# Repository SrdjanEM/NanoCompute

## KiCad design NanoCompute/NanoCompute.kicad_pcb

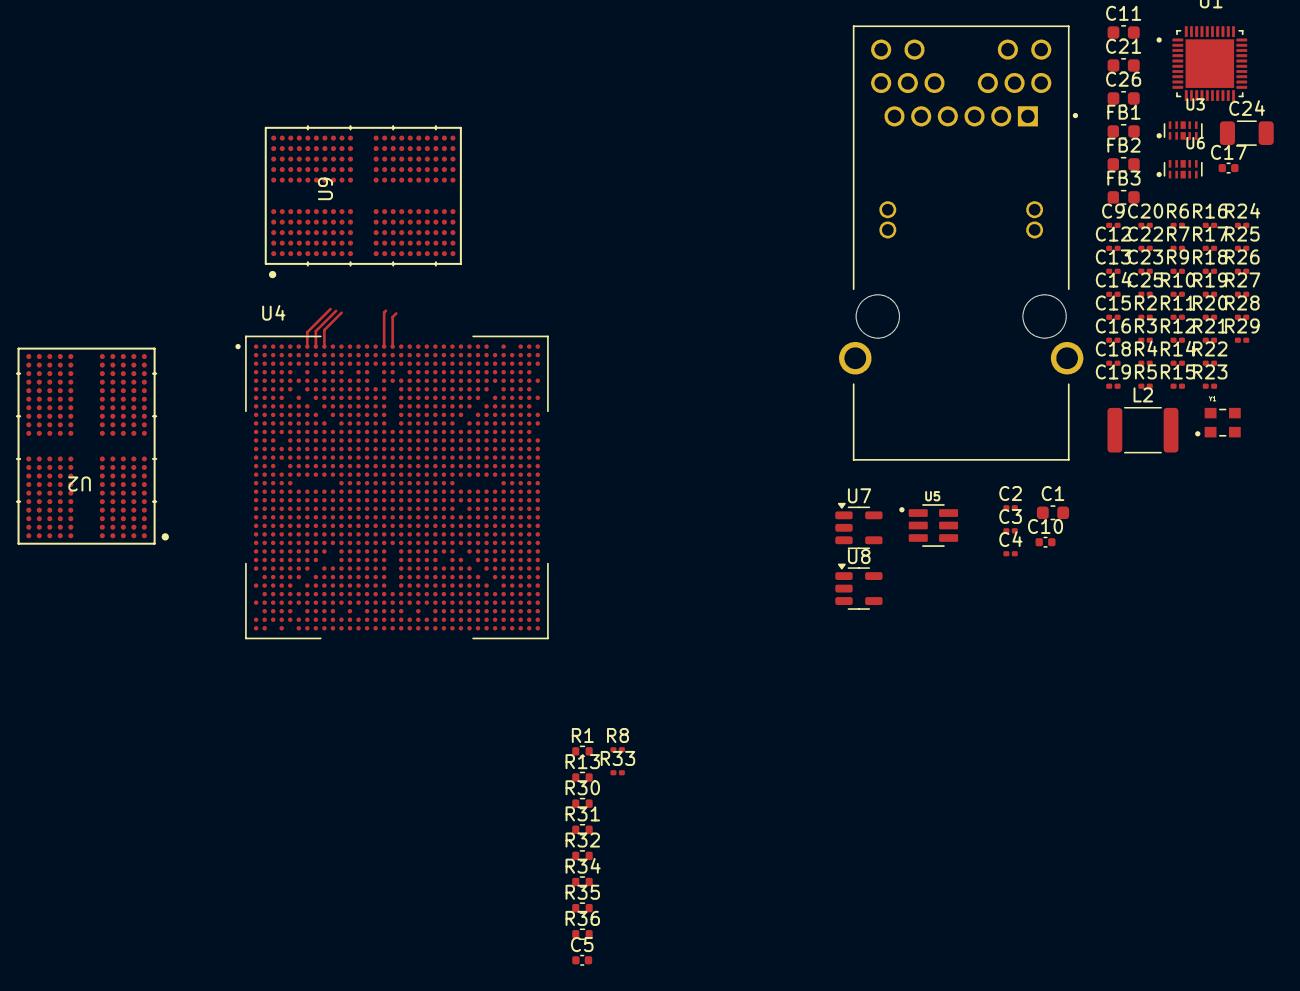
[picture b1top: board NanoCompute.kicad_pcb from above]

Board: 2 copper layers, 74 parts (0 on the bottom side), 184 nets.

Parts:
C1, C11, C21, C26: 10u; C_0603_1608Metric
C2: 1u; C_0201_0603Metric
C3, C9, C12, C13, C14, C15, C16, C18, C19, C20, C22, C23, C25: 100n; C_0201_0603Metric
C4: 10n; C_0201_0603Metric
C5: 100n; C_0402_1005Metric
C10, C17: 4u7; C_0402_1005Metric
C24: 1n / 2kV; C_1206_3216Metric
FB1, FB2, FB3: 120R @ 100MHz; L_0603_1608Metric
J1: 2250506; BEL_2250506-1
L2: 2u2; L_1812_4532Metric
R1, R13, R30, R31, R32, R34, R35, R36: 240R; R_0402_1005Metric
R2, R3, R4, R5, R6, R7: 33R; R_0201_0603Metric
R8, R33: 10K; R_0201_0603Metric
R9, R10, R11, R14, R15, R16, R17, R18, R19, R20, R21, R22, R23, R24, R25, R26, R27: 4K7; R_0201_0603Metric
R12: 1K5; R_0201_0603Metric
R28, R29: 510R; R_0201_0603Metric
U1: RTL8211F; RTL8211F-CG
U2, U9: MT53E1G32D2FW; VFBGA200_10X14.5X1.1FW_MRN
U3, U6: HSP051; IC_HSP051-4M10
U4: RK3588; BGA1088C65P34X34_2300X2300X204N
U5: TPS54308; TPS54308DDCR
U7: TLV74311; SOT-23-5
U8: TLV74325; SOT-23-5
Y1: 25 MHz; OSC_ECS-2520S25-250-FN-TR

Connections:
+1V8: C16.1, FB3.1
+1VA8: C21.1, C22.1, FB3.2, R9.1, U1.28 (DVDD_RG)
+3V3: C9.1, C11.1, FB2.1, R11.1, R12.1, R15.1, R17.1, R25.1, U1.13 (MDC), U1.29 (DVDD33), Y1.4 (VDD)
+3VA3: C12.1, C13.1, FB2.2, R19.1, R20.1, R24.1, U1.11 (AVDD33), U1.40 (AVDD33)
/Ethernet PHY/ETH_HWRESET: C23.1, R9.2, U1.12 (PHYRSTB)
/Ethernet PHY/ETH_MDUI: R12.2, U1.14 (MDIO)
/Ethernet PHY/ETH_RESET: R10.1, U1.39 (RSET)
/Ethernet PHY/LED0/CFG_EXT: J1.20, R25.2, U1.32 (LED0/CFG_EXT)
/Ethernet PHY/LED1/CFG_LDO0: J1.18, R27.1, U1.33 (LED1/CFG_LDO0)
/Ethernet PHY/LED2/CFG_LDO1: R26.1, U1.34 (LED2/CFG_LDO1)
/Ethernet PHY/PHYAD0: R5.2, R11.2, R14.1
/Ethernet PHY/PHYAD1: R6.2, R15.2, R16.1
/Ethernet PHY/PHYAD2: R7.2, R17.2, R18.1
/Ethernet PHY/PHY_ADVDDL: C15.1, C19.1, C20.1, FB1.2, U1.3 (AVDD10), U1.8 (AVDD10), U1.38 (AVDD10)
/Ethernet PHY/PHY_DVDDL: C14.1, C17.1, C18.1, FB1.1, L2.2, U1.21 (DVDD10)
/Ethernet PHY/PLLOFF: R4.2, R23.1, R24.2
/Ethernet PHY/RXDLY: R2.2, R19.2, R21.1
/Ethernet PHY/TP_1_N: J1.10 (TRD1-), U1.2 (MDIN0), U3.2 (I/O_2)
/Ethernet PHY/TP_1_P: J1.11 (TRD1+), U1.1 (MDIP0), U3.1 (I/O_1)
/Ethernet PHY/TP_2_N: J1.5 (TRD2-), U1.5 (MDIN1), U3.5 (I/O_4)
/Ethernet PHY/TP_2_P: J1.4 (TRD2+), U1.4 (MDIP1), U3.4 (I/O_3)
/Ethernet PHY/TP_3_N: J1.2 (TRD3-), U1.7 (MDIN2), U6.2 (I/O_2)
/Ethernet PHY/TP_3_P: J1.3 (TRD3+), U1.6 (MDIP2), U6.1 (I/O_1)
/Ethernet PHY/TP_4_N: J1.9 (TRD4-), U1.10 (MDIN3), U6.5 (I/O_4)
/Ethernet PHY/TP_4_P: J1.8 (TRD4+), U1.9 (MDIP3), U6.4 (I/O_3)
/Ethernet PHY/TRCTx: C25.1, C26.1, J1.1 (TRCT3), J1.6 (TRCT2), J1.7 (TRCT4), J1.12 (TRCT1)
/Ethernet PHY/TXDLY: R3.2, R20.2, R22.1
/LPDDR4/CA0_A: U2.H2 (CA0_A), U4.T7 (DDR_CH0_A0_A)
/LPDDR4/CA0_B: U2.R2 (CA0_B), U4.M8 (DDR_CH0_A0_B)
/LPDDR4/CA0_C: U4.G12 (DDR_CH1_A0_C), U9.H2 (CA0_A)
/LPDDR4/CA0_D: U4.H15 (DDR_CH1_A0_D), U9.R2 (CA0_B)
/LPDDR4/CA1_A: U2.J2 (CA1_A), U4.T8 (DDR_CH0_A1_A)
/LPDDR4/CA1_B: U2.P2 (CA1_B), U4.M5 (DDR_CH0_A1_B)
/LPDDR4/CA1_C: U4.F12 (DDR_CH1_A1_C), U9.J2 (CA1_A)
/LPDDR4/CA1_D: U4.G14 (DDR_CH1_A1_D), U9.P2 (CA1_B)
/LPDDR4/CA2_A: U2.H9 (CA2_A), U4.P4 (DDR_CH0_A2_A)
/LPDDR4/CA2_B: U2.R9 (CA2_B), U4.N5 (DDR_CH0_A2_B)
/LPDDR4/CA2_C: U4.E13 (DDR_CH1_A2_C), U9.H9 (CA2_A)
/LPDDR4/CA2_D: U4.G13 (DDR_CH1_A2_D), U9.R9 (CA2_B)
/LPDDR4/CA3_A: U2.H10 (CA3_A), U4.P5 (DDR_CH0_A3_A)
/LPDDR4/CA3_B: U2.R10 (CA3_B), U4.N4 (DDR_CH0_A3_B)
/LPDDR4/CA3_C: U4.D13 (DDR_CH1_A3_C), U9.H10 (CA3_A)
/LPDDR4/CA3_D: U4.E14 (DDR_CH1_A3_D), U9.R10 (CA3_B)
/LPDDR4/CA4_A: U2.H11 (CA4_A), U4.R1 (DDR_CH0_A4_A)
/LPDDR4/CA4_B: U2.R11 (CA4_B), U4.K1 (DDR_CH0_A4_B)
/LPDDR4/CA4_C: U4.A10 (DDR_CH1_A4_C), U9.H11 (CA4_A)
/LPDDR4/CA4_D: U4.A15 (DDR_CH1_A4_D), U9.R11 (CA4_B)
/LPDDR4/CA5_A: U2.J11 (CA5_A), U4.P2 (DDR_CH0_A5_A)
/LPDDR4/CA5_B: U2.P11 (CA5_B), U4.L2 (DDR_CH0_A5_B)
/LPDDR4/CA5_C: U4.B11 (DDR_CH1_A5_C), U9.J11 (CA5_A)
/LPDDR4/CA5_D: U4.B14 (DDR_CH1_A5_D), U9.P11 (CA5_B)
/LPDDR4/CKE0_A: U2.J4 (CKE0_A), U4.P7 (DDR_CH0_LP4/4X_CKE0/LP5_CS0_A)
/LPDDR4/CKE0_B: U2.P4 (CKE0_B), U4.L5 (DDR_CH0_LP4/4X_CKE0/LP5_CS0_B)
/LPDDR4/CKE0_C: U4.D11 (DDR_CH1_LP4/4X_CKE0/LP5_CS0_C), U9.J4 (CKE0_A)
/LPDDR4/CKE0_D: U4.D16 (DDR_CH1_LP4/4X_CKE0/LP5_CS0_D), U9.P4 (CKE0_B)
/LPDDR4/CKE1_A: U2.J5 (CKE1_A), U4.N7 (DDR_CH0_LP4/4X_CKE1/LP5_CS1_A)
/LPDDR4/CKE1_B: U2.P5 (CKE1_B), U4.L4 (DDR_CH0_LP4/4X_CKE1/LP5_CS1_B)
/LPDDR4/CKE1_C: U4.E11 (DDR_CH1_LP4/4X_CKE1/LP5_CS1_C), U9.J5 (CKE1_A)
/LPDDR4/CKE1_D: U4.E16 (DDR_CH1_LP4/4X_CKE1/LP5_CS1_D), U9.P5 (CKE1_B)
/LPDDR4/CK_A_N: U2.J9 (CK_c_A), U2.P9 (CK_c_B), U4.M1 (DDR_CH0_CKB_B), U4.N1 (DDR_CH0_CKB_A)
/LPDDR4/CK_A_P: U2.J8 (CK_t_A), U2.P8 (CK_t_B), U4.M2 (DDR_CH0_CK_B), U4.N2 (DDR_CH0_CK_A)
/LPDDR4/CK_C_N: U4.A12 (DDR_CH1_CKB_C), U9.J9 (CK_c_A)
/LPDDR4/CK_C_P: U4.B12 (DDR_CH1_CK_C), U9.J8 (CK_t_A)
/LPDDR4/CK_D_N: U4.A13 (DDR_CH1_CKB_D), U9.P9 (CK_c_B)
/LPDDR4/CK_D_P: U4.B13 (DDR_CH1_CK_D), U9.P8 (CK_t_B)
/LPDDR4/CS0_A: U2.H4 (CS0_A), U4.R6 (DDR_CH0_LP4/4X_CS0_A)
/LPDDR4/CS0_B: U2.R4 (CS0_B), U4.L7 (DDR_CH0_LP4/4X_CS0_B)
/LPDDR4/CS0_C: U4.G11 (DDR_CH1_LP4/4X_CS0_C), U9.H4 (CS0_A)
/LPDDR4/CS0_D: U4.E19 (DDR_CH1_LP4/4X_CS0_D), U9.R4 (CS0_B)
/LPDDR4/CS1_A: U2.H3 (CS1_A), U4.R7 (DDR_CH0_LP4/4X_CS1_A)
/LPDDR4/CS1_B: U2.R3 (CS1_B), U4.L8 (DDR_CH0_LP4/4X_CS1_B)
/LPDDR4/CS1_C: U4.H11 (DDR_CH1_LP4/4X_CS1_C), U9.H3 (CS1_A)
/LPDDR4/CS1_D: U4.D19 (DDR_CH1_LP4/4X_CS1_D), U9.R3 (CS1_B)
/LPDDR4/DMI1_A: U2.C10 (DMI1_A), U4.AB4 (DDR_CH0_DM1_A)
/LPDDR4/DMI1_B: U2.Y10 (DMI1_B), U4.E4 (DDR_CH0_DM1_B)
/LPDDR4/DMI1_C: U4.D4 (DDR_CH1_DM1_C), U9.C10 (DMI1_A)
/LPDDR4/DMI1_D: U4.D22 (DDR_CH1_DM1_D), U9.Y10 (DMI1_B)
/LPDDR4/DMIO_A: U2.C3 (DMI0_A), U4.Y4 (DDR_CH0_DM0_A)
/LPDDR4/DMIO_B: U2.Y3 (DMI0_B), U4.G4 (DDR_CH0_DM0_B)
/LPDDR4/DMIO_C: U4.F8 (DDR_CH1_DM0_C), U9.C3 (DMI0_A)
/LPDDR4/DMIO_D: U4.D20 (DDR_CH1_DM0_D), U9.Y3 (DMI0_B)
/LPDDR4/DQ0_A: U2.B2 (DQ0_A), U4.U1 (DDR_CH0_DQ0_A)
/LPDDR4/DQ0_B: U2.AA2 (DQ0_B), U4.H1 (DDR_CH0_DQ0_B)
/LPDDR4/DQ0_C: U4.A8 (DDR_CH1_DQ0_C), U9.B2 (DQ0_A)
/LPDDR4/DQ0_D: U4.A17 (DDR_CH1_DQ0_D), U9.AA2 (DQ0_B)
/LPDDR4/DQ1_A: U2.C2 (DQ1_A), U4.T2 (DDR_CH0_DQ1_A)
/LPDDR4/DQ1_B: U2.Y2 (DQ1_B), U4.J2 (DDR_CH0_DQ1_B)
/LPDDR4/DQ1_C: U4.B9 (DDR_CH1_DQ1_C), U9.C2 (DQ1_A)
/LPDDR4/DQ1_D: U4.B16 (DDR_CH1_DQ1_D), U9.Y2 (DQ1_B)
/LPDDR4/DQ2_A: U2.E2 (DQ2_A), U4.T1 (DDR_CH0_DQ2_A)
/LPDDR4/DQ2_B: U2.V2 (DQ2_B), U4.J1 (DDR_CH0_DQ2_B)
/LPDDR4/DQ2_C: U4.A9 (DDR_CH1_DQ2_C), U9.E2 (DQ2_A)
/LPDDR4/DQ2_D: U4.A16 (DDR_CH1_DQ2_D), U9.V2 (DQ2_B)
/LPDDR4/DQ3_A: U2.F2 (DQ3_A), U4.R2 (DDR_CH0_DQ3_A)
/LPDDR4/DQ3_B: U2.U2 (DQ3_B), U4.K2 (DDR_CH0_DQ3_B)
/LPDDR4/DQ3_C: U4.B10 (DDR_CH1_DQ3_C), U9.F2 (DQ3_A)
/LPDDR4/DQ3_D: U4.B15 (DDR_CH1_DQ3_D), U9.U2 (DQ3_B)
/LPDDR4/DQ4_A: U2.F4 (DQ4_A), U4.W1 (DDR_CH0_DQ4_A)
/LPDDR4/DQ4_B: U2.U4 (DQ4_B), U4.F1 (DDR_CH0_DQ4_B)
/LPDDR4/DQ4_C: U4.A6 (DDR_CH1_DQ4_C), U9.F4 (DQ4_A)
/LPDDR4/DQ4_D: U4.A19 (DDR_CH1_DQ4_D), U9.U4 (DQ4_B)
/LPDDR4/DQ5_A: U2.E4 (DQ5_A), U4.V2 (DDR_CH0_DQ5_A)
/LPDDR4/DQ5_B: U2.V4 (DQ5_B), U4.G2 (DDR_CH0_DQ5_B)
/LPDDR4/DQ5_C: U4.B7 (DDR_CH1_DQ5_C), U9.E4 (DQ5_A)
/LPDDR4/DQ5_D: U4.B18 (DDR_CH1_DQ5_D), U9.V4 (DQ5_B)
/LPDDR4/DQ6_A: U2.C4 (DQ6_A), U4.V1 (DDR_CH0_DQ6_A)
/LPDDR4/DQ6_B: U2.Y4 (DQ6_B), U4.G1 (DDR_CH0_DQ6_B)
/LPDDR4/DQ6_C: U4.A7 (DDR_CH1_DQ6_C), U9.C4 (DQ6_A)
/LPDDR4/DQ6_D: U4.A18 (DDR_CH1_DQ6_D), U9.Y4 (DQ6_B)
/LPDDR4/DQ7_A: U2.B4 (DQ7_A), U4.U2 (DDR_CH0_DQ7_A)
/LPDDR4/DQ7_B: U2.AA4 (DQ7_B), U4.H2 (DDR_CH0_DQ7_B)
/LPDDR4/DQ7_C: U4.B8 (DDR_CH1_DQ7_C), U9.B4 (DQ7_A)
/LPDDR4/DQ7_D: U4.B17 (DDR_CH1_DQ7_D), U9.AA4 (DQ7_B)
/LPDDR4/DQ8_A: U2.B11 (DQ8_A), U4.AB2 (DDR_CH0_DQ8_A)
/LPDDR4/DQ8_B: U2.AA11 (DQ8_B), U4.D2 (DDR_CH0_DQ8_B)
/LPDDR4/DQ8_C: U4.A3 (DDR_CH1_DQ8_C), U9.B11 (DQ8_A)
/LPDDR4/DQ8_D: U4.A22 (DDR_CH1_DQ8_D), U9.AA11 (DQ8_B)
/LPDDR4/DQ9_A: U2.C11 (DQ9_A), U4.AB1 (DDR_CH0_DQ9_A)
/LPDDR4/DQ9_B: U2.Y11 (DQ9_B), U4.C1 (DDR_CH0_DQ9_B)
/LPDDR4/DQ9_C: U4.B3 (DDR_CH1_DQ9_C), U9.C11 (DQ9_A)
/LPDDR4/DQ9_D: U4.B22 (DDR_CH1_DQ9_D), U9.Y11 (DQ9_B)
/LPDDR4/DQ10_A: U2.E11 (DQ10_A), U4.AC1 (DDR_CH0_DQ10_A)
/LPDDR4/DQ10_B: U2.V11 (DQ10_B), U4.C2 (DDR_CH0_DQ10_B)
/LPDDR4/DQ10_C: U4.A2 (DDR_CH1_DQ10_C), U9.E11 (DQ10_A)
/LPDDR4/DQ10_D: U4.A23 (DDR_CH1_DQ10_D), U9.V11 (DQ10_B)
/LPDDR4/DQ11_A: U2.F11 (DQ11_A), U4.AC2 (DDR_CH0_DQ11_A)
/LPDDR4/DQ11_B: U2.U11 (DQ11_B), U4.B1 (DDR_CH0_DQ11_B)
/LPDDR4/DQ11_C: U4.B2 (DDR_CH1_DQ11_C), U9.F11 (DQ11_A)
/LPDDR4/DQ11_D: U4.B23 (DDR_CH1_DQ11_D), U9.U11 (DQ11_B)
/LPDDR4/DQ12_A: U2.F9 (DQ12_A), U4.Y1 (DDR_CH0_DQ12_A)
/LPDDR4/DQ12_B: U2.U9 (DQ12_B), U4.F2 (DDR_CH0_DQ12_B)
/LPDDR4/DQ12_C: U4.A5 (DDR_CH1_DQ12_C), U9.F9 (DQ12_A)
/LPDDR4/DQ12_D: U4.A20 (DDR_CH1_DQ12_D), U9.U9 (DQ12_B)
/LPDDR4/DQ13_A: U2.E9 (DQ13_A), U4.Y2 (DDR_CH0_DQ13_A)
/LPDDR4/DQ13_B: U2.V9 (DQ13_B), U4.E1 (DDR_CH0_DQ13_B)
/LPDDR4/DQ13_C: U4.B5 (DDR_CH1_DQ13_C), U9.E9 (DQ13_A)
/LPDDR4/DQ13_D: U4.B20 (DDR_CH1_DQ13_D), U9.V9 (DQ13_B)
/LPDDR4/DQ14_A: U2.C9 (DQ14_A), U4.AA1 (DDR_CH0_DQ14_A)
/LPDDR4/DQ14_B: U2.Y9 (DQ14_B), U4.E2 (DDR_CH0_DQ14_B)
/LPDDR4/DQ14_C: U4.A4 (DDR_CH1_DQ14_C), U9.C9 (DQ14_A)
/LPDDR4/DQ14_D: U4.A21 (DDR_CH1_DQ14_D), U9.Y9 (DQ14_B)
/LPDDR4/DQ15_A: U2.B9 (DQ15_A), U4.AA2 (DDR_CH0_DQ15_A)
/LPDDR4/DQ15_B: U2.AA9 (DQ15_B), U4.D1 (DDR_CH0_DQ15_B)
/LPDDR4/DQ15_C: U4.B4 (DDR_CH1_DQ15_C), U9.B9 (DQ15_A)
/LPDDR4/DQ15_D: U4.B21 (DDR_CH1_DQ15_D), U9.AA9 (DQ15_B)
/LPDDR4/DQS0_A_N: U2.E3 (DQS0_c_A), U4.U4 (DDR_CH0_DQS0N_A)
/LPDDR4/DQS0_A_P: U2.D3 (DQS0_t_A), U4.U5 (DDR_CH0_DQS0P_A)
/LPDDR4/DQS0_B_N: U2.V3 (DQS0_c_B), U4.J7 (DDR_CH0_DQS0N_B)
/LPDDR4/DQS0_B_P: U2.W3 (DQS0_t_B), U4.J8 (DDR_CH0_DQS0P_B)
/LPDDR4/DQS0_C_N: U4.D9 (DDR_CH1_DQS0N_C), U9.E3 (DQS0_c_A)
/LPDDR4/DQS0_C_P: U4.E9 (DDR_CH1_DQS0P_C), U9.D3 (DQS0_t_A)
/LPDDR4/DQS0_D_N: U4.G16 (DDR_CH1_DQS0N_D), U9.V3 (DQS0_c_B)
/LPDDR4/DQS0_D_P: U4.H16 (DDR_CH1_DQS0P_D), U9.W3 (DQS0_t_B)
/LPDDR4/DQS1_A_N: U2.E10 (DQS1_c_A), U4.AA4 (DDR_CH0_DQS1N_A)
/LPDDR4/DQS1_A_P: U2.D10 (DQS1_t_A), U4.AA5 (DDR_CH0_DQS1P_A)
/LPDDR4/DQS1_B_N: U2.V10 (DQS1_c_B), U4.F4 (DDR_CH0_DQS1N_B)
/LPDDR4/DQS1_B_P: U2.W10 (DQS1_t_B), U4.F5 (DDR_CH0_DQS1P_B)
/LPDDR4/DQS1_C_N: U4.D5 (DDR_CH1_DQS1N_C), U9.E10 (DQS1_c_A)
/LPDDR4/DQS1_C_P: U4.E5 (DDR_CH1_DQS1P_C), U9.D10 (DQS1_t_A)
/LPDDR4/DQS1_D_N: U4.E21 (DDR_CH1_DQS1N_D), U9.V10 (DQS1_c_B)
/LPDDR4/DQS1_D_P: U4.D21 (DDR_CH1_DQS1P_D), U9.W10 (DQS1_t_B)
/LPDDR4/~RESET_AB: R8.1, U2.T11 (RESET_n), U4.T4 (DDR_CH0_RESET_A)
/LPDDR4/~RESET_CD: R33.1, U4.E10 (DDR_CH1_RESET_C), U9.T11 (RESET_n)
GND: C9.2, C11.2, C12.2, C13.2, C14.2, C15.2, C16.2, C17.2, C18.2, C19.2, C20.2, C21.2, C22.2, C23.2, C24.2, C25.2, C26.2, R8.2, R10.2, R14.2, R16.2, R18.2, R21.2, R22.2, R23.2, R26.2, R27.2, R28.2, R29.2, R30.2, R31.2, R33.2, R35.2, R36.2, U1.36 (XTAL_IN), U1.41 (GND), U2.A3 (VSS), U2.A10 (VSS), U2.AB3 (VSS), U2.AB5 (VSS), U2.AB8 (VSS), U2.AB10 (VSS), U2.C1 (VSS), U2.C5 (VSS), U2.C8 (VSS), U2.C12 (VSS), U2.D2 (VSS), U2.D4 (VSS), U2.D9 (VSS), U2.D11 (VSS), U2.E1 (VSS), U2.E5 (VSS), U2.E8 (VSS), U2.E12 (VSS), U2.G1 (VSS), U2.G3 (VSS), U2.G5 (VSS), U2.G8 (VSS), U2.G10 (VSS), U2.G12 (VSS), U2.J1 (VSS), U2.J3 (VSS), U2.J10 (VSS), U2.J12 (VSS), U2.K2 (VSS), U2.K4 (VSS), U2.K9 (VSS), U2.K11 (VSS), U2.N2 (VSS), U2.N4 (VSS), U2.N9 (VSS), U2.N11 (VSS), U2.P1 (VSS), U2.P3 (VSS), U2.P10 (VSS), U2.P12 (VSS), U2.T1 (VSS), U2.T3 (VSS), U2.T5 (VSS), U2.T8 (VSS), U2.T10 (VSS), U2.T12 (VSS), U2.V1 (VSS), U2.V5 (VSS), U2.V8 (VSS), U2.V12 (VSS), U2.W2 (VSS), U2.W4 (VSS), U2.W9 (VSS), U2.W11 (VSS), U2.Y1 (VSS), U2.Y5 (VSS), U2.Y8 (VSS), U2.Y12 (VSS), U3.3 (GND), U3.8 (GND__1), U4.L16 (DDR_CH1_PLL_AVSS), U4.M11 (DDR_CH0_PLL_AVSS), U6.3 (GND), U6.8 (GND__1), U9.A3 (VSS), U9.A10 (VSS), U9.AB3 (VSS), U9.AB5 (VSS), U9.AB8 (VSS), U9.AB10 (VSS), U9.C1 (VSS), U9.C5 (VSS), U9.C8 (VSS), U9.C12 (VSS), U9.D2 (VSS), U9.D4 (VSS), U9.D9 (VSS), U9.D11 (VSS), U9.E1 (VSS), U9.E5 (VSS), U9.E8 (VSS), U9.E12 (VSS), U9.G1 (VSS), U9.G3 (VSS), U9.G5 (VSS), U9.G8 (VSS), U9.G10 (VSS), U9.G12 (VSS), U9.J1 (VSS), U9.J3 (VSS), U9.J10 (VSS), U9.J12 (VSS), U9.K2 (VSS), U9.K4 (VSS), U9.K9 (VSS), U9.K11 (VSS), U9.N2 (VSS), U9.N4 (VSS), U9.N9 (VSS), U9.N11 (VSS), U9.P1 (VSS), U9.P3 (VSS), U9.P10 (VSS), U9.P12 (VSS), U9.T1 (VSS), U9.T3 (VSS), U9.T5 (VSS), U9.T8 (VSS), U9.T10 (VSS), U9.T12 (VSS), U9.V1 (VSS), U9.V5 (VSS), U9.V8 (VSS), U9.V12 (VSS), U9.W2 (VSS), U9.W4 (VSS), U9.W9 (VSS), U9.W11 (VSS), U9.Y1 (VSS), U9.Y5 (VSS), U9.Y8 (VSS), U9.Y12 (VSS), Y1.2 (GND)
unnamed: C24.1, J1.S1 (SHIELD), J1.S2 (SHIELD)
unnamed: J1.17, R29.1
unnamed: J1.19, R28.1
unnamed: L2.1, U1.30 (REG_OUT)
unnamed: R7.1, U1.26 (RXCTL/PHYAD2)
unnamed: R6.1, U1.27 (RXC/PHYAD1)
unnamed: R2.1, U1.25 (RXD0/RXDLY)
unnamed: R3.1, U1.24 (RXD1/TXDLY)
unnamed: R4.1, U1.23 (RXD2/PLLOFF)
unnamed: R5.1, U1.22 (RXD3/PHYAD0)
unnamed: U1.37 (XTAL_OUT/EXT_CLK), Y1.3 (OUTPUT)
unnamed: R13.2, U2.A5 (ZQ0)
unnamed: R1.2, U2.A8 (ZQ1)
unnamed: R30.1, U4.W8 (DDR_CH0_ZQ_A)
unnamed: R31.1, U4.H7 (DDR_CH0_ZQ_B)
unnamed: R35.1, U4.G8 (DDR_CH1_ZQ_C)
unnamed: R36.1, U4.F18 (DDR_CH1_ZQ_D)
unnamed: R34.2, U9.A5 (ZQ0)
unnamed: R32.2, U9.A8 (ZQ1)
VDD2_DDR: R1.1, R13.1, R32.1, R34.1, U2.G2 (ODT_CA_A), U2.T2 (ODT_CA_B), U9.G2 (ODT_CA_A), U9.T2 (ODT_CA_B)

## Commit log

2025-01-01 Added inital work done for Gigabit Ethernet (RGMII) and LPDRR4
2025-01-02 I think I added net classes(+coloring) for LPDDR4.
    I'm not sure, it's 3AM I should check what I did tomorrow, figure our
    those couple of signals that I don't understand where to connect or what
    they are for. Probabbly could start working on the power section of the
    LPDDR4. Need to check how much RAM will I actually need for 4K video
    (@60fps?).
2025-01-03 Finished one LPDDR4 and connected it to LPDDR4 PHY
    Connected the LPDDR4 to RK3588 LPDDR4 PHY, check all connections and it LGTM!
    Added a second chip for additional 32Gb(4GB) LPDDR4 for total of 64Gb(8GB) of LPDRR4 memory.
    Need to change nets for second chip from A->C and B->D.
2025-01-04 LPDDR4 second chip connected to LPDDR4 PHY
    Added a missing Units for second LPDDR4 chip (VSS and Power).
    Added a 1x100nF decoupling capacitor for each power rail of VDD1 but it
    seems too much. Might need to find a better way of doing Low-Mid-High
    range frequency decoupling.
    Added TPS65296 as a LPddr4 Memory power solution but I need to check if
    I can power both memory chips with just one TPS65296.
2025-01-05 Added 2 HDMI 2.1 connectors
    Will delay working on any kind of power system since I'm still figuring
    out what I will have on this board. Would prefer to have a PMIC than
    bunch of DC-DC regulators.
2025-01-06 Added eMMC 5.1 HS400 128GB
    It would act as a on-board primary storage while NVMe would act as an
    extension/upgrade.
2025-01-06 Added net labels for eMMC
